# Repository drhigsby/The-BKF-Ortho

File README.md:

# The-BKF-Ortho
 The base kit forty - ortho edition

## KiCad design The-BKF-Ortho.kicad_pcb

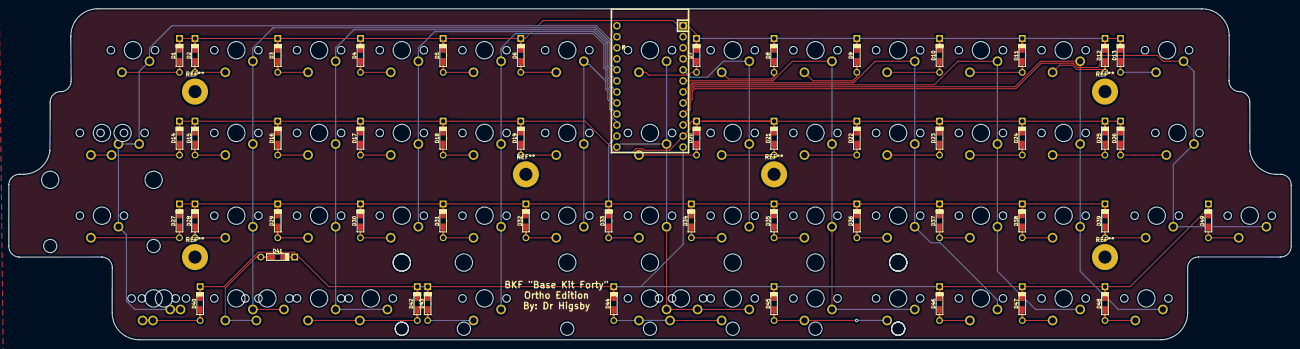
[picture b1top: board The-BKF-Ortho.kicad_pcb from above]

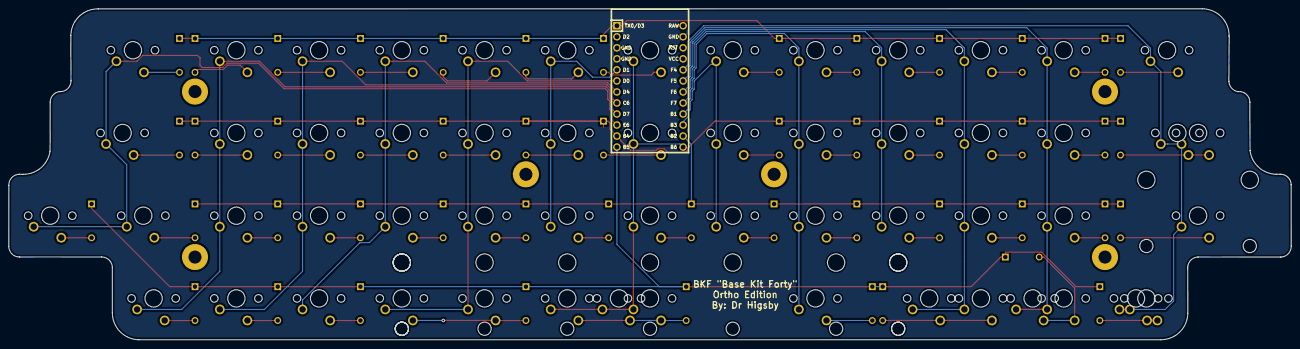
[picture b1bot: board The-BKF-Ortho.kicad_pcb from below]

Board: 2 copper layers, 295.3 x 76.2 mm, 106 parts (50 on the bottom side), 67 nets.

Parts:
D1, D2, D3, D4, D5, D6, D7, D8, D9, D10, D11, D12, D13, D14, D15, D16, D17, D18, D19, D20, D21, D22, D23, D24, D25, D26, D27, D28, D29, D30, D31, D32, D33, D34, D35, D36, D37, D38, D39, D40, D41, D42, D43, D44, D45, D46, D47, D48, D49: D_Small; Diode-Hybrid-Back
MX1, MX13: MX-NoLED; MXOnly-1.5U-NoLED
MX2, MX3, MX4, MX5, MX6, MX7, MX8, MX9, MX10, MX11, MX12, MX15, MX16, MX17, MX18, MX19, MX20, MX21, MX22, MX23, MX24, MX25, MX28, MX29, MX30, MX31, MX32, MX33, MX34, MX35, MX36, MX37, MX38, MX40, MX41, MX42, MX45-1u1, MX46, MX47, MX48, MX49: MX-NoLED; MXOnly-1U-NoLED
MX14, MX26: MX-NoLED; MXOnly-1.75U-NoLED
MX14A1, MX39, MX40-1.25u1, MX41-1.25u1, MX42-1.25u1: MX-NoLED; MXOnly-1.25U-NoLED
MX27: MX-NoLED; MXOnly-2.25U-NoLED
MX43, MX44-3u1, MX45-3u1: MX-NoLED; MXOnly-3U-NoLED
MX44-6.25u1: MX-NoLED; MXOnly-6.25U-NoLED
MX44-7u1: MX-NoLED; MXOnly-7U-NoLED
U1: ProMicro; ArduinoProMicro

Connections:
GND: U1.3, U1.4, U1.23
unnamed: D1.2, MX1.2
unnamed: D2.2, MX2.2
unnamed: D3.2, MX3.2
unnamed: D4.2, MX4.2
unnamed: D5.2, MX5.2
unnamed: D6.2, MX6.2
unnamed: D7.2, MX7.2
unnamed: D8.2, MX8.2
unnamed: D9.2, MX9.2
unnamed: D10.2, MX10.2
unnamed: D11.2, MX11.2
unnamed: D12.2, MX12.2
unnamed: D13.2, MX13.2
unnamed: D14.2, MX14.2, MX14A1.2
unnamed: D15.2, MX15.2
unnamed: D16.2, MX16.2
unnamed: D17.2, MX17.2
unnamed: D18.2, MX18.2
unnamed: D19.2, MX19.2
unnamed: D20.2, MX20.2
unnamed: D21.2, MX21.2
unnamed: D22.2, MX22.2
unnamed: D23.2, MX23.2
unnamed: D24.2, MX24.2
unnamed: D25.2, MX25.2
unnamed: D26.2, MX26.2
unnamed: D27.2, MX27.2
unnamed: D28.2, MX28.2
unnamed: D29.2, MX29.2
unnamed: D30.2, MX30.2
unnamed: D31.2, MX31.2
unnamed: D32.2, MX32.2
unnamed: D33.2, MX33.2
unnamed: D34.2, MX34.2
unnamed: D35.2, MX35.2
unnamed: D36.2, MX36.2
unnamed: D37.2, MX37.2
unnamed: D38.2, MX38.2
unnamed: D39.2, MX39.2
unnamed: D40.2, MX40.2, MX40-1.25u1.2
unnamed: D41.2, MX41.2, MX41-1.25u1.2
unnamed: D42.2, MX42.2, MX42-1.25u1.2
unnamed: D43.2, MX43.2
unnamed: D44.2, MX44-3u1.2, MX44-6.25u1.2, MX44-7u1.2
unnamed: D45.2, MX45-1u1.2, MX45-3u1.2
unnamed: D46.2, MX46.2
unnamed: D47.2, MX47.2
unnamed: D48.2, MX48.2
unnamed: D49.2, MX49.2
col0: MX1.1, MX14.1, MX14A1.1, MX27.1, MX40.1, MX40-1.25u1.1, U1.20
col1: MX2.1, MX15.1, MX28.1, MX41.1, MX41-1.25u1.1, U1.19
col2: MX3.1, MX16.1, MX29.1, MX42.1, MX42-1.25u1.1, U1.18
col3: MX4.1, MX17.1, MX30.1, U1.17
col4: MX5.1, MX18.1, MX31.1, MX43.1, U1.16
col5: MX6.1, MX19.1, MX32.1, U1.15
col6: MX7.1, MX20.1, MX33.1, MX44-3u1.1, MX44-6.25u1.1, MX44-7u1.1, U1.13
col7: MX8.1, MX21.1, MX34.1, U1.5
col8: MX9.1, MX22.1, MX35.1, MX45-1u1.1, MX45-3u1.1, U1.6
col9: MX10.1, MX23.1, MX36.1, MX46.1, U1.7
col10: MX11.1, MX24.1, MX37.1, MX47.1, U1.8
col11: MX12.1, MX25.1, MX38.1, MX48.1, U1.9
col12: MX13.1, MX26.1, MX39.1, MX49.1, U1.10
row0: D1.1, D2.1, D3.1, D4.1, D5.1, D6.1, D7.1, D8.1, D9.1, D10.1, D11.1, D12.1, D13.1, U1.1
row1: D14.1, D15.1, D16.1, D17.1, D18.1, D19.1, D20.1, D21.1, D22.1, D23.1, D24.1, D25.1, D26.1, U1.11
row2: D27.1, D28.1, D29.1, D30.1, D31.1, D32.1, D33.1, D34.1, D35.1, D36.1, D37.1, D38.1, D39.1, U1.14
row3: D40.1, D41.1, D42.1, D43.1, D44.1, D45.1, D46.1, D47.1, D48.1, D49.1, U1.12
